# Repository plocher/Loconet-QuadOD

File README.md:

# Loconet-QuadOD
## License: CERN Open Hardware Licence v1.2

A variation on [IO4-QuadOD](https://github.com/plocher/IO4-QuadOD) that replaces the
WemosD1 & IO4 connections with an Arduino Pro Mini and LocoNet-style
communications.

This simple 4-pack module should end up with a BOM cost between $5
and $10, so a full stand alone quad detector pack would run about
$60 with detector boards.

The [MRRWA Embedded Loconet library](https://github.com/mrrwa/LocoNet)
includes support for LN-SV V2 configuration management, which is
also supported by JMRI; it should be pretty easy to write an
addressable Detector sketch (TBD) with assorted XML definitions
suitable for DecoderPro3...

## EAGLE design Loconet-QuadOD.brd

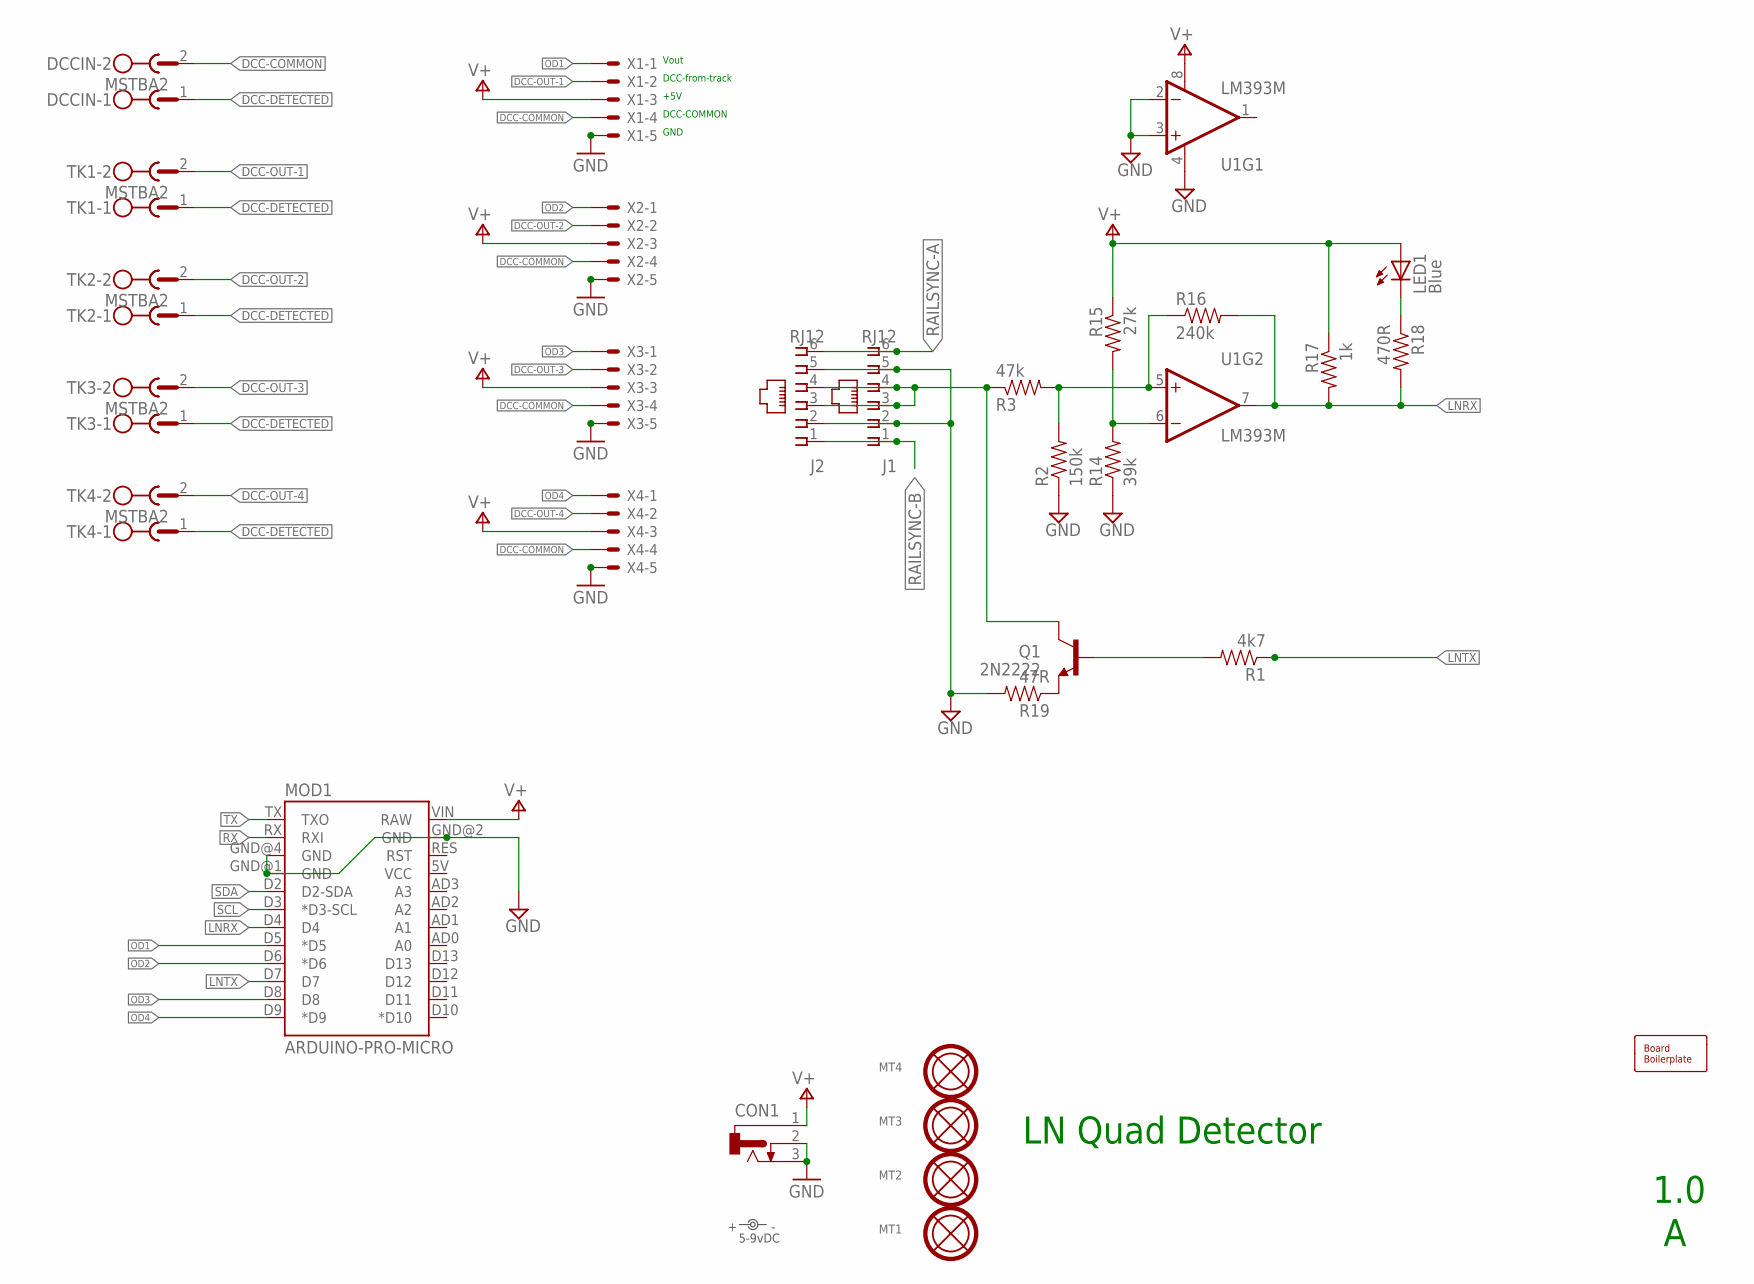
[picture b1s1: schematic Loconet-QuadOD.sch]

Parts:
BOARD1: BOARD100X100-NOHOLES; BOARD-SEEED10X10-NOHOLES
CON1: CONNECTOR-DC-POWER-RA; DCJ0202
DCCIN: MSTBA2
J1, J2: RJ12; RJ25
LED1: Blue; 0805-LED
MOD1: ARDUINO-PRO-MICRO; ARDUINO-PRO-MICRO-NOSILK
MT1, MT2, MT3, MT4: MOUNTINGHOLE
Q1: 2N2222; SOT23
R1: 4k7; 0805-RES
R2: 150k; 0805-RES
R3: 47k; 0805-RES
R14: 39k; 0805-RES
R15: 27k; 0805-RES
R16: 240k; 0805-RES
R17: 1k; 0805-RES
R18: 470R; 0805-RES
R19: 47R; 0805-RES
TK1, TK2, TK3, TK4: MSTBA2
U1: LM393M; SO08
U$1: 5-9vDC; PWR_LABEL
X1, X2, X3, X4: KK-156-5

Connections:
DCC-COMMON: DCCIN.2, X1.4, X2.4, X3.4, X4.4
DCC-DETECTED: DCCIN.1, TK1.1, TK2.1, TK3.1, TK4.1
DCC-OUT-1: TK1.2, X1.2
DCC-OUT-2: TK2.2, X2.2
DCC-OUT-3: TK3.2, X3.2
DCC-OUT-4: TK4.2, X4.2
GND: CON1.2, CON1.3, J1.2, J1.5, J2.2, J2.5, MOD1.GND@1 (GND), MOD1.GND@2 (GND), MOD1.GND@4 (GND), R2.1, R14.1, R19.2, U1.2 (-IN), U1.3 (+IN), U1.4 (V-), X1.5, X2.5, X3.5, X4.5
LNRX: MOD1.D4, R16.2, R17.2, R18.2, U1.7 (OUT)
LNTX: MOD1.D7, R1.1
LOCONET: J1.3, J1.4, J2.3, J2.4, Q1.3 (C), R3.1
unnamed: Q1.1 (B), R1.2
unnamed: LED1.C, R18.1
unnamed: R2.2, R3.2, R16.1, U1.5 (+IN)
unnamed: R14.2, R15.2, U1.6 (-IN)
unnamed: Q1.2 (E), R19.1
OD1: MOD1.D5 (*D5), X1.1
OD2: MOD1.D6 (*D6), X2.1
OD3: MOD1.D8, X3.1
OD4: MOD1.D9 (*D9), X4.1
RAILSYNC-A: J1.6, J2.6
RAILSYNC-B: J1.1, J2.1
RX: MOD1.RX (RXI)
SCL: MOD1.D3 (*D3-SCL)
SDA: MOD1.D2 (D2-SDA)
TX: MOD1.TX (TXO)
V+: CON1.1, LED1.A, MOD1.VIN (RAW), R15.1, R17.1, U1.8 (V+), X1.3, X2.3, X3.3, X4.3

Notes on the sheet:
LN Quad Detector
1.0
Vout
DCC-from-track
+5V
DCC-COMMON
GND

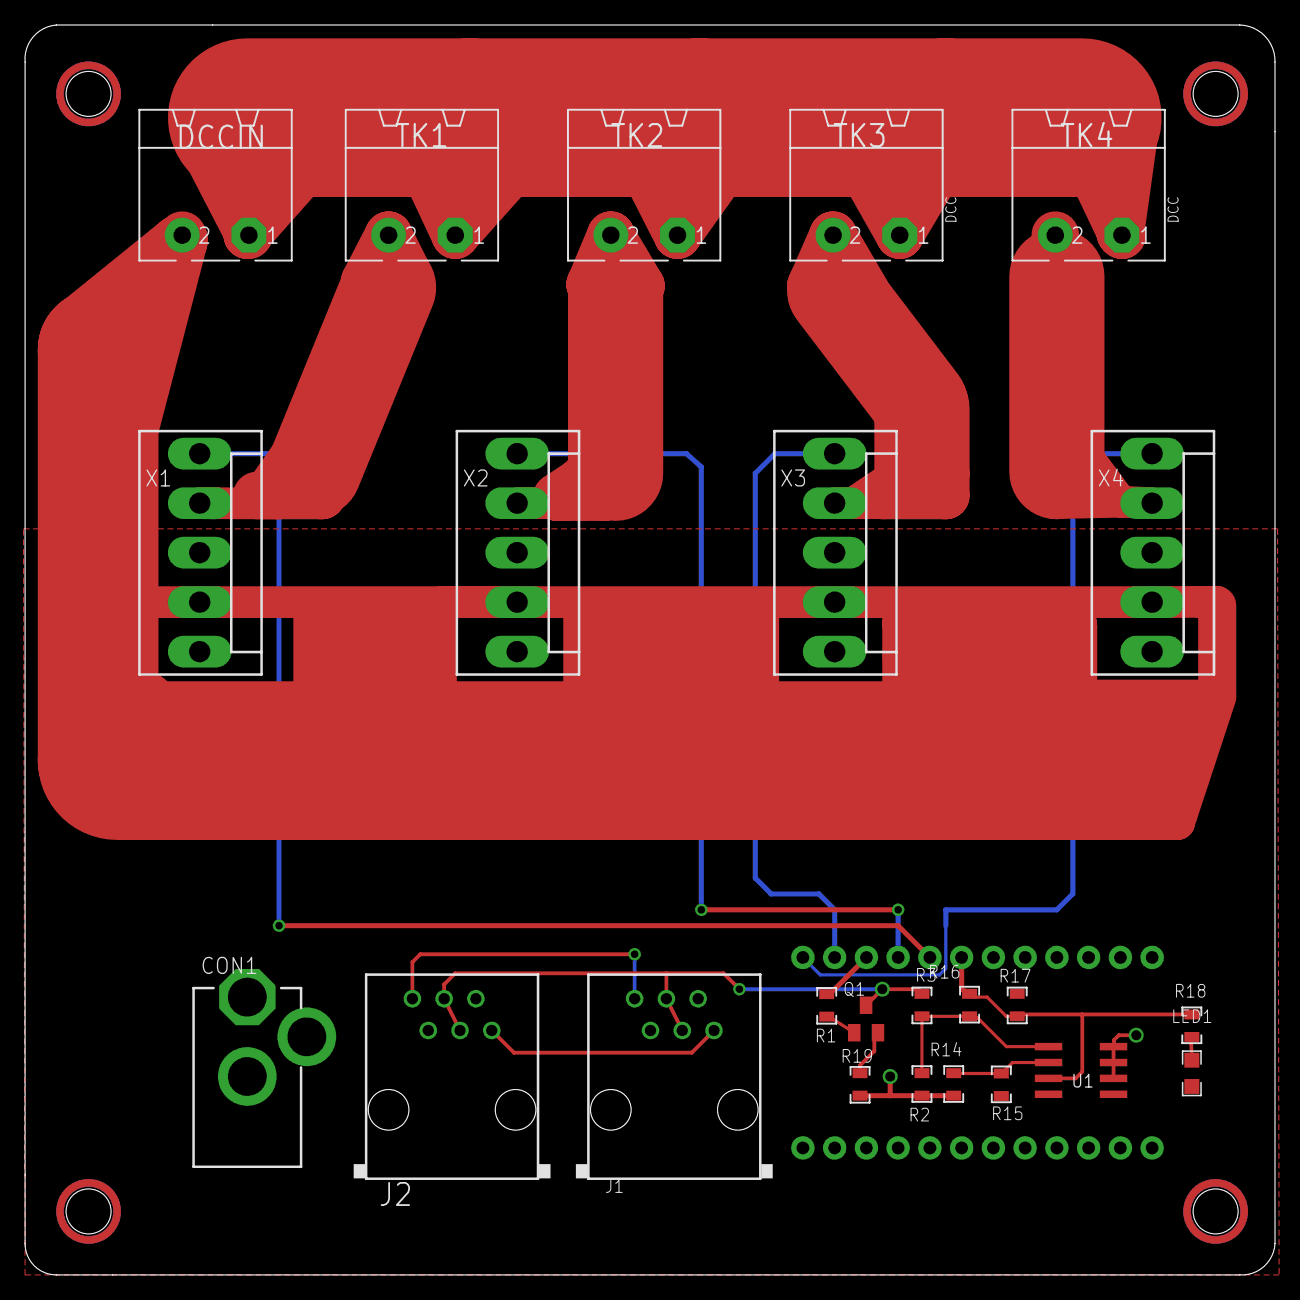
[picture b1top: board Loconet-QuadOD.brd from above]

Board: 2 copper layers, 100.0 x 100.0 mm, 31 parts (0 on the bottom side), 22 nets.

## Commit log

2019-12-08 added graphic
2020-05-04 updated tags
2020-09-19 Obsolete
